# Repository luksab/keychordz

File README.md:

# Keychordz

This is my first completely custom keyboard hardware/software.

## Hardware

The hardware design is done in [KiCad](https://www.kicad.org/) and can be found in the hardware folder.

## Software

I started configuring [QMK](https://docs.qmk.fm/#/) for this hardware, but the chording features turned out to be too limiting, so I decided to write my own firmware from scratch in [Rust](https://rust-lang.org/).

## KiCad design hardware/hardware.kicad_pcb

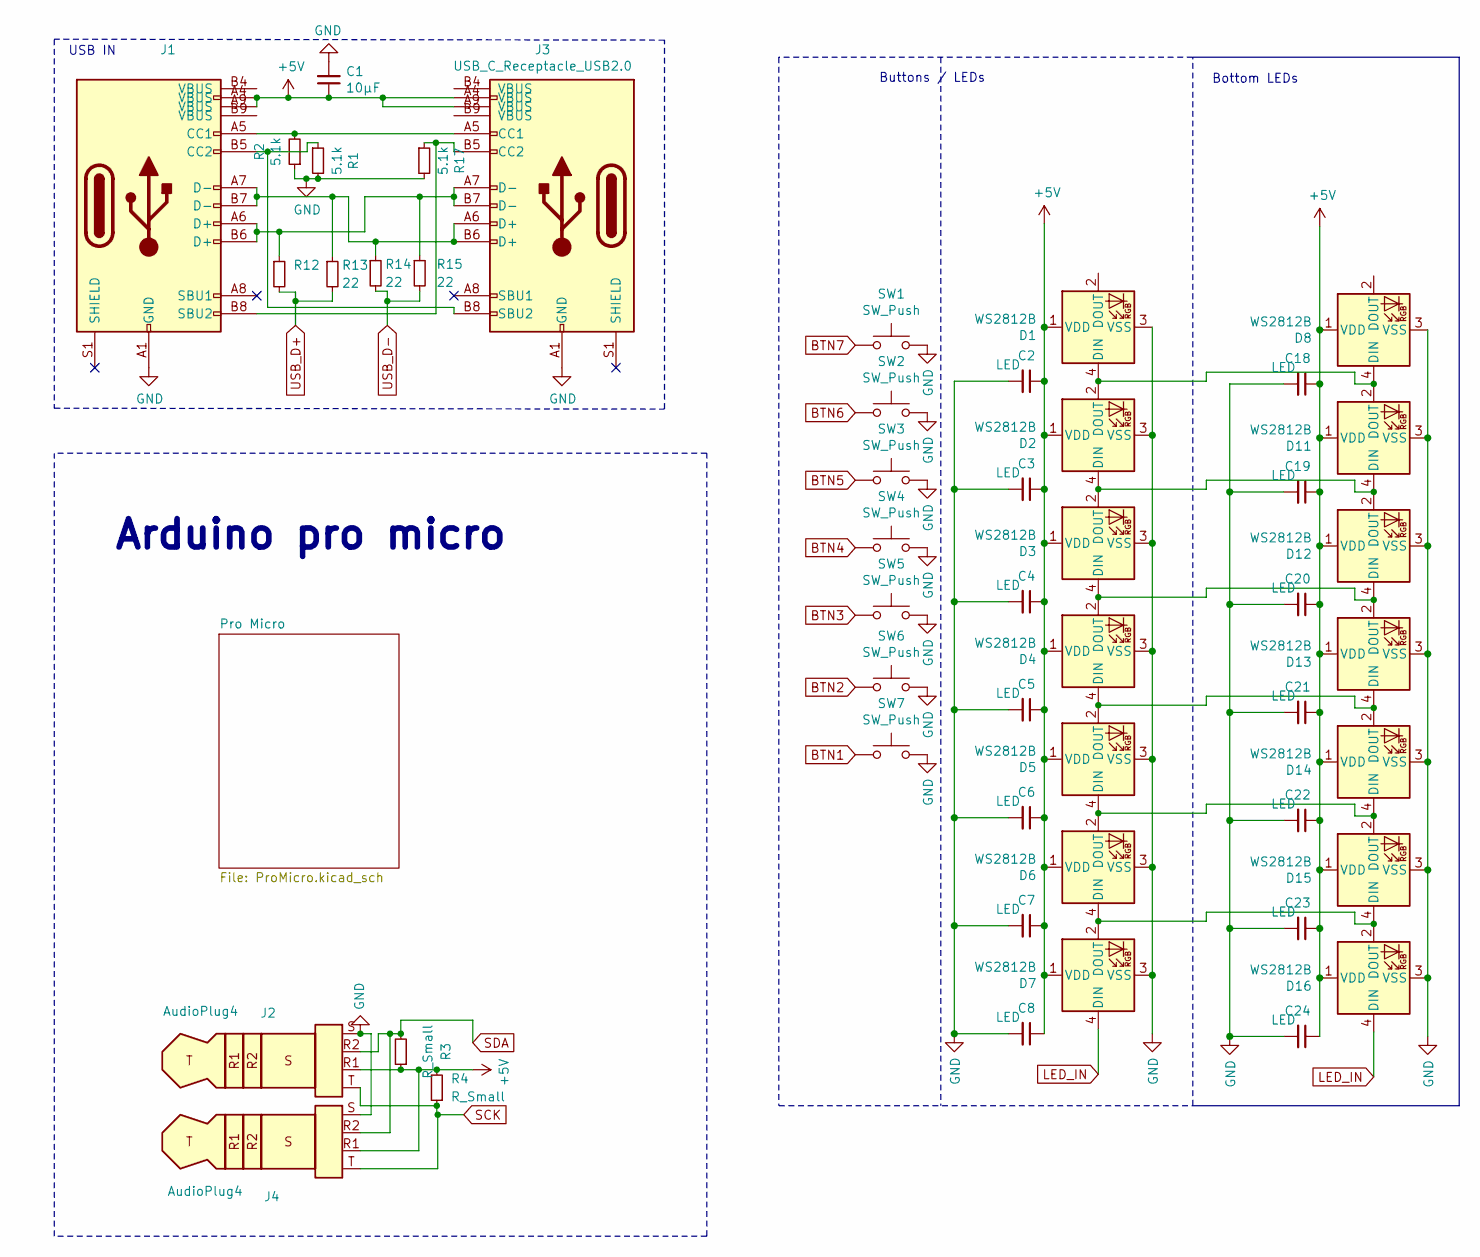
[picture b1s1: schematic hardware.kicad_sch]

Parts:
C1: 10µF; C_0805_2012Metric_Pad1.18x1.45mm_HandSolder
C2, C3, C4, C5, C6, C7, C8, C18, C19, C20, C21, C22, C23, C24: LED; C_0603_1608Metric_Pad1.08x0.95mm_HandSolder
D1, D2, D3, D4, D5, D6, D7, D8, D11, D12, D13, D14, D15, D16: WS2812B; LED_WS2812B_PLCC4_2.2x2.2mm
J1: (no value)
J2, J4: AudioPlug4; Jack_3.5mm_PJ320D_Horizontal
J3: USB_C_Receptacle_USB2.0; SS52400002
R1, R2, R17: 5.1k; R_0603_1608Metric_Pad0.98x0.95mm_HandSolder
R3, R4: R_Small; R_0603_1608Metric_Pad0.98x0.95mm_HandSolder
R12: (no value)
R13, R14, R15: 22; R_0603_1608Metric_Pad0.98x0.95mm_HandSolder
SW1, SW2, SW3, SW4, SW5, SW6, SW7: SW_Push; SW_PG1350

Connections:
+5V: C1.1, C2.1, C3.1, C4.1, C5.1, C6.1, C7.1, C8.1, C18.1, C19.1, C20.1, C21.1, C22.1, C23.1, C24.1, D1.1 (VDD), D2.1 (VDD), D3.1 (VDD), D4.1 (VDD), D5.1 (VDD), D6.1 (VDD), D7.1 (VDD), D8.1 (VDD), D11.1 (VDD), D12.1 (VDD), D13.1 (VDD), D14.1 (VDD), D15.1 (VDD), D16.1 (VDD), J1.A4 (VBUS), J1.A9 (VBUS), J2.R1, J3.A4 (VBUS), J3.A9 (VBUS), J4.R1, R3.1, R4.2; also elsewhere on the board
BTN1: SW7.1; also elsewhere on the board
BTN2: SW6.1; also elsewhere on the board
BTN3: SW5.1; also elsewhere on the board
BTN4: SW4.1; also elsewhere on the board
BTN5: SW3.1; also elsewhere on the board
BTN6: SW2.1; also elsewhere on the board
BTN7: SW1.1; also elsewhere on the board
GND: C1.2, C2.2, C3.2, C4.2, C5.2, C6.2, C7.2, C8.2, C18.2, C19.2, C20.2, C21.2, C22.2, C23.2, C24.2, D1.3 (VSS), D2.3 (VSS), D3.3 (VSS), D4.3 (VSS), D5.3 (VSS), D6.3 (VSS), D7.3 (VSS), D8.3 (VSS), D11.3 (VSS), D12.3 (VSS), D13.3 (VSS), D14.3 (VSS), D15.3 (VSS), D16.3 (VSS), J1.A1 (GND), J1.A12 (GND), J1.B1 (GND), J1.B12 (GND), J2.S, J3.A1 (GND), J3.A12 (GND), J3.B1 (GND), J3.B12 (GND), J4.S, R1.2, R2.1, R17.2, SW1.2, SW2.2, SW3.2, SW4.2, SW5.2, SW6.2, SW7.2; also elsewhere on the board
LED_IN: D7.4 (DIN), D16.4 (DIN); also elsewhere on the board
unnamed: D1.4 (DIN), D2.2 (DOUT), D8.4 (DIN), D11.2 (DOUT)
unnamed: D2.4 (DIN), D3.2 (DOUT), D11.4 (DIN), D12.2 (DOUT)
unnamed: D3.4 (DIN), D4.2 (DOUT), D12.4 (DIN), D13.2 (DOUT)
unnamed: D4.4 (DIN), D5.2 (DOUT), D13.4 (DIN), D14.2 (DOUT)
unnamed: D6.4 (DIN), D7.2 (DOUT), D15.4 (DIN), D16.2 (DOUT)
unnamed: D5.4 (DIN), D6.2 (DOUT), D14.4 (DIN), D15.2 (DOUT)
unnamed: J1.A5 (CC1), J3.A5 (CC1), R2.2
unnamed: J1.B5 (CC2), J3.B8 (SBU2), R1.1
unnamed: J1.B8 (SBU2), J3.B5 (CC2), R17.1
unnamed 40: J1.A7 (D-), J1.B7 (D-), J3.A6 (D+), J3.B6 (D+), R13.1, R14.1; also elsewhere on the board
unnamed 43: J1.A6 (D+), J1.B6 (D+), J3.A7 (D-), J3.B7 (D-), R12.1, R15.1; also elsewhere on the board
SCK: J2.T, J4.T, R4.1; also elsewhere on the board
SDA: J2.R2, J4.R2, R3.2; also elsewhere on the board
USB_D+: R12.2, R13.2; also elsewhere on the board
USB_D-: R14.2, R15.2; also elsewhere on the board

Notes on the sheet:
Arduino pro micro
Buttons / LEDs
Bottom LEDs
USB IN

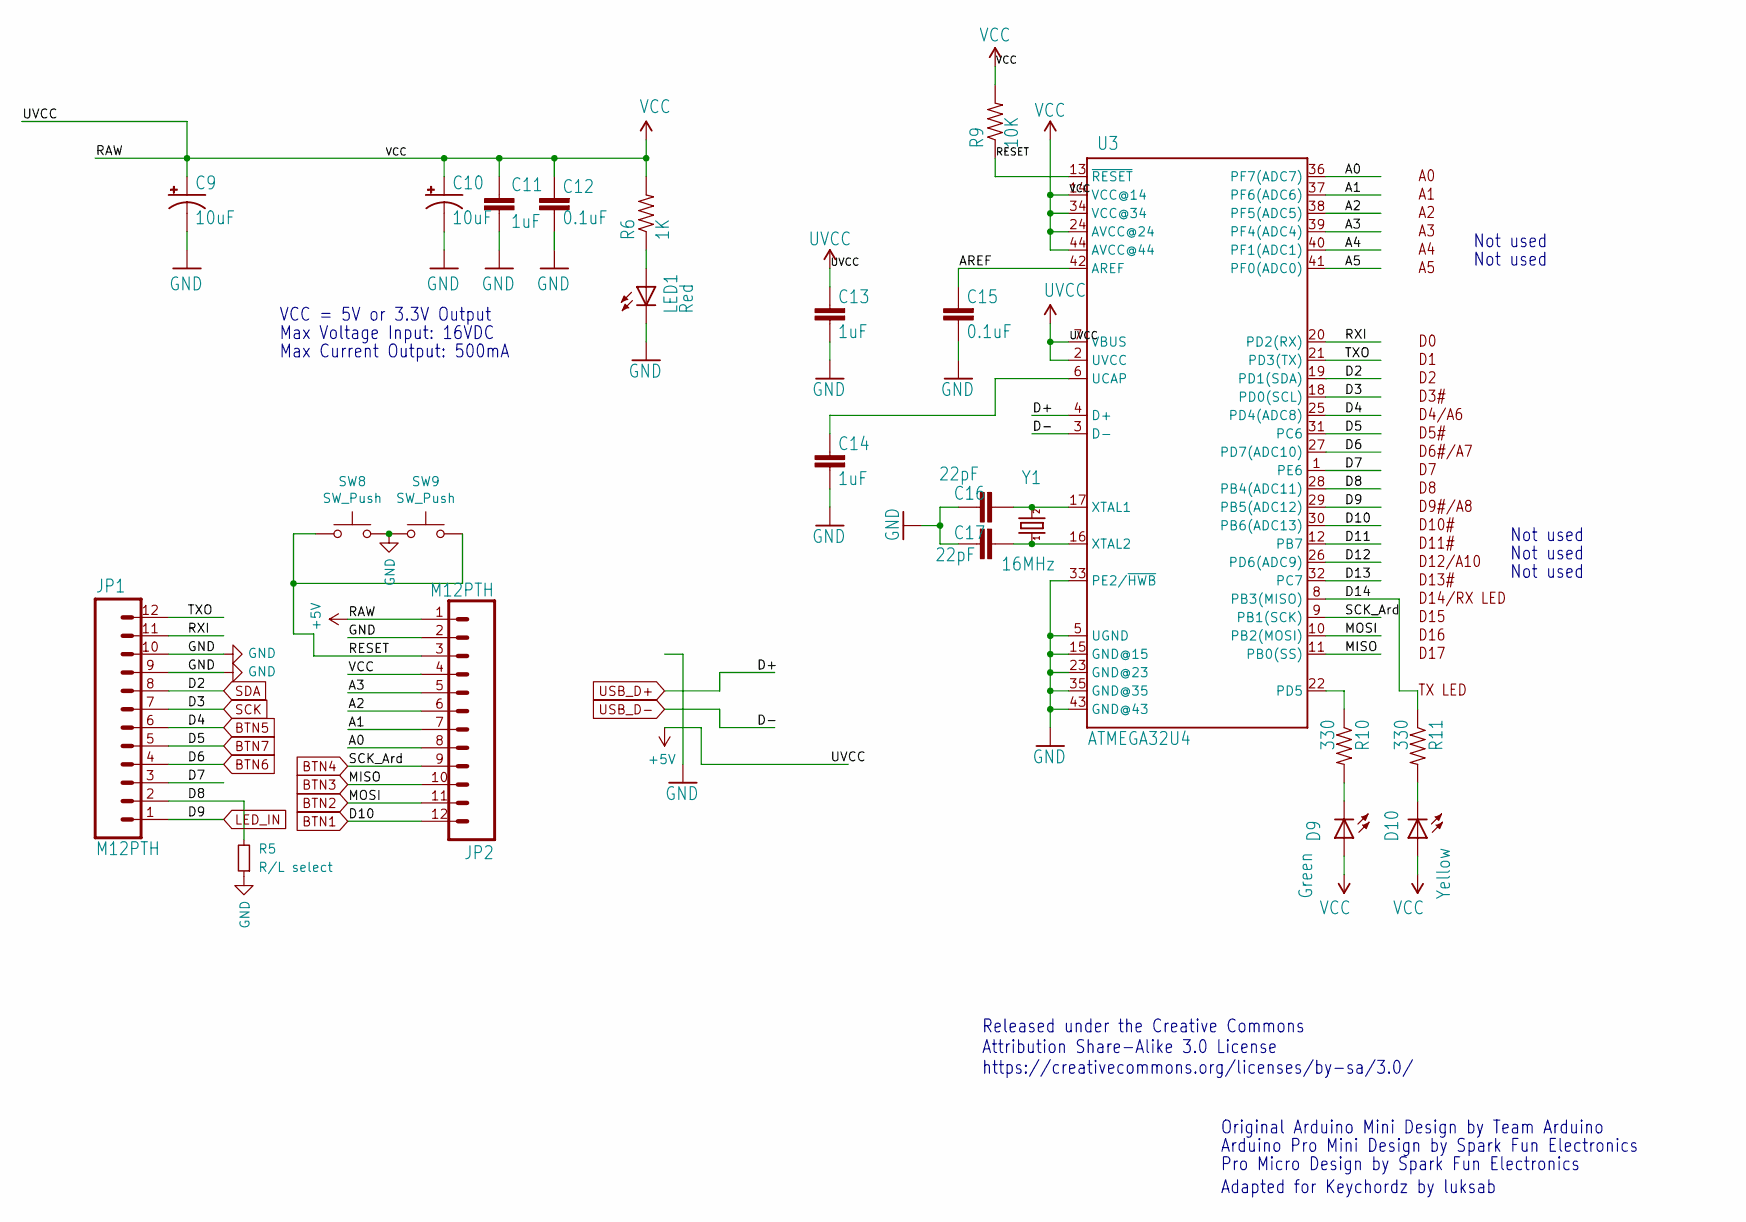
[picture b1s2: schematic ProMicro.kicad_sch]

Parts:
C9, C10: 10uF; EIA3216
C11, C13, C14: 1uF; C_0603_1608Metric_Pad1.08x0.95mm_HandSolder
C12, C15: 0.1uF; C_0603_1608Metric_Pad1.08x0.95mm_HandSolder
C16, C17: 22pF; C_0603_1608Metric_Pad1.08x0.95mm_HandSolder
D9: Green; LED_0603_1608Metric_Pad1.05x0.95mm_HandSolder
D10: Yellow; LED_0603_1608Metric_Pad1.05x0.95mm_HandSolder
JP1, JP2: M12PTH; PinHeader_1x12_P2.54mm_Vertical
LED1: Red; LED_0603_1608Metric_Pad1.05x0.95mm_HandSolder
R5: R/L select; R_0805_2012Metric_Pad1.20x1.40mm_HandSolder
R6: 1K; R_0603_1608Metric_Pad0.98x0.95mm_HandSolder
R9: 10K; R_0603_1608Metric_Pad0.98x0.95mm_HandSolder
R10, R11: 330; R_0603_1608Metric_Pad0.98x0.95mm_HandSolder
SW8, SW9: SW_Push; SW_SPST_CK_RS282G05A3
U3: ATMEGA32U4; QFN-44-NOPAD_1_1-OUTFAKES
Y1: 16MHz; CRYSTAL-SMD-5X3

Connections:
+5V: C9.A (+), C10.A (+), C11.1, C12.2, C13.2, D9.2 (A), D10.2 (A), JP2.1, JP2.4, R6.2, R9.2, U3.2 (UVCC), U3.7 (VBUS), U3.14 (VCC@14), U3.24 (AVCC@24), U3.34 (VCC@34), U3.44 (AVCC@44); also elsewhere on the board
/Pro Micro/A0: JP2.8, U3.36 (PF7(ADC7))
/Pro Micro/A1: JP2.7, U3.37 (PF6(ADC6))
/Pro Micro/A2: JP2.6, U3.38 (PF5(ADC5))
/Pro Micro/A3: JP2.5, U3.39 (PF4(ADC4))
/Pro Micro/A4: U3.40 (PF1(ADC1))
/Pro Micro/A5: U3.41 (PF0(ADC0))
/Pro Micro/AREF: C15.2, U3.42 (AREF)
/Pro Micro/D7: JP1.3, U3.1 (PE6)
/Pro Micro/D8: JP1.2, R5.2, U3.28 (PB4(ADC11))
/Pro Micro/D11: U3.12 (PB7)
/Pro Micro/D12: U3.26 (PD6(ADC9))
/Pro Micro/D13: U3.32 (PC7)
/Pro Micro/D14: R11.1, U3.8 (PB3(MISO))
/Pro Micro/RESET: JP2.3, R9.1, SW8.1, SW9.2, U3.13 (~RESET)
/Pro Micro/RXI: JP1.11, U3.20 (PD2(RX))
/Pro Micro/TXO: JP1.12, U3.21 (PD3(TX))
BTN1: JP2.12, U3.30 (PB6(ADC13)); also elsewhere on the board
BTN2: JP2.11, U3.10 (PB2(MOSI)); also elsewhere on the board
BTN3: JP2.10, U3.11 (PB0(SS)); also elsewhere on the board
BTN4: JP2.9, U3.9 (PB1(SCK)); also elsewhere on the board
BTN5: JP1.6, U3.25 (PD4(ADC8)); also elsewhere on the board
BTN6: JP1.4, U3.27 (PD7(ADC10)); also elsewhere on the board
BTN7: JP1.5, U3.31 (PC6); also elsewhere on the board
GND: C9.C (-), C10.C (-), C11.2, C12.1, C13.1, C14.1, C15.1, C16.2, C17.2, JP1.9, JP1.10, JP2.2, LED1.1 (C), R5.1, SW8.2, SW9.1, U3.5 (UGND), U3.15 (GND@15), U3.23 (GND@23), U3.33 (PE2/~HWB), U3.35 (GND@35), U3.43 (GND@43); also elsewhere on the board
LED_IN: JP1.1, U3.29 (PB5(ADC12)); also elsewhere on the board
unnamed: C14.2, U3.6 (UCAP)
unnamed: C16.1, U3.17 (XTAL1), Y1.3 (2)
unnamed: C17.1, U3.16 (XTAL2), Y1.1
unnamed: D9.1 (K), R10.2
unnamed: D10.1 (K), R11.2
unnamed: LED1.2 (A), R6.1
unnamed: R10.1, U3.22 (PD5)
SCK: JP1.7, U3.18 (PD0(SCL)); also elsewhere on the board
SDA: JP1.8, U3.19 (PD1(SDA)); also elsewhere on the board
USB_D+: U3.4 (D+); also elsewhere on the board
USB_D-: U3.3 (D-); also elsewhere on the board

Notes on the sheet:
VCC = 5V or 3.3V Output
Arduino Pro Mini Design by Spark Fun Electronics
Original Arduino Mini Design by Team Arduino
Released under the Creative Commons Attribution Share-Alike 3.0 License https://creativecommons.org/licenses/by-sa/3.0/
Pro Micro Design by Spark Fun Electronics
Adapted for Keychordz by luksab
Not used
Max Current Output: 500mA
Max Voltage Input: 16VDC

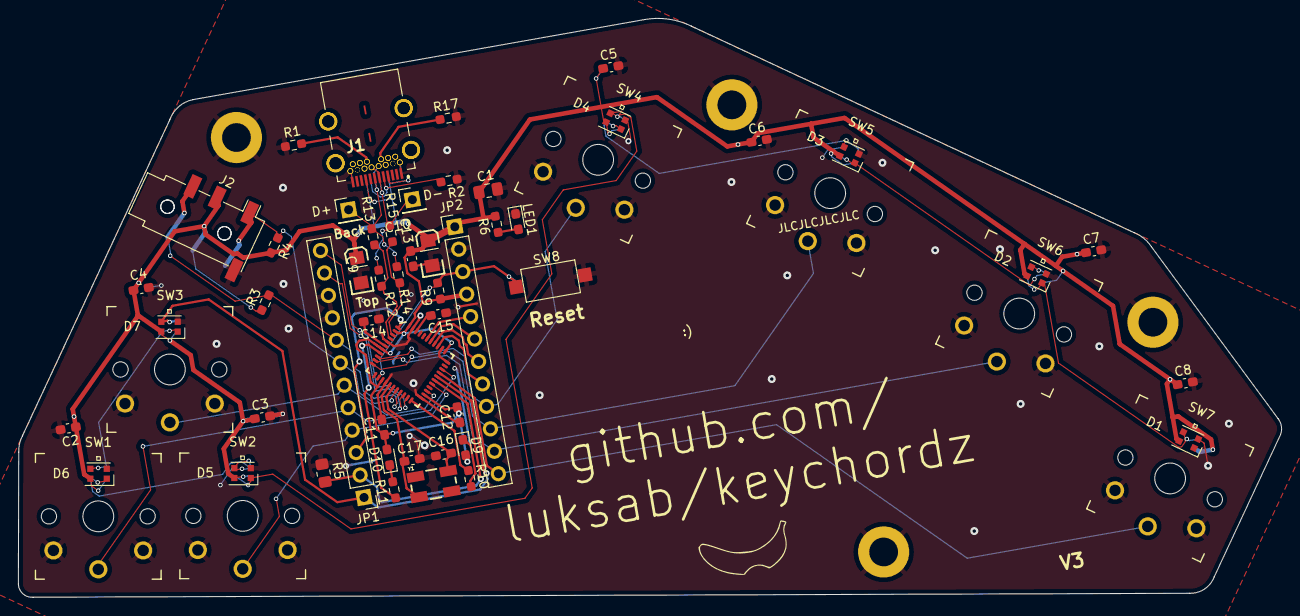
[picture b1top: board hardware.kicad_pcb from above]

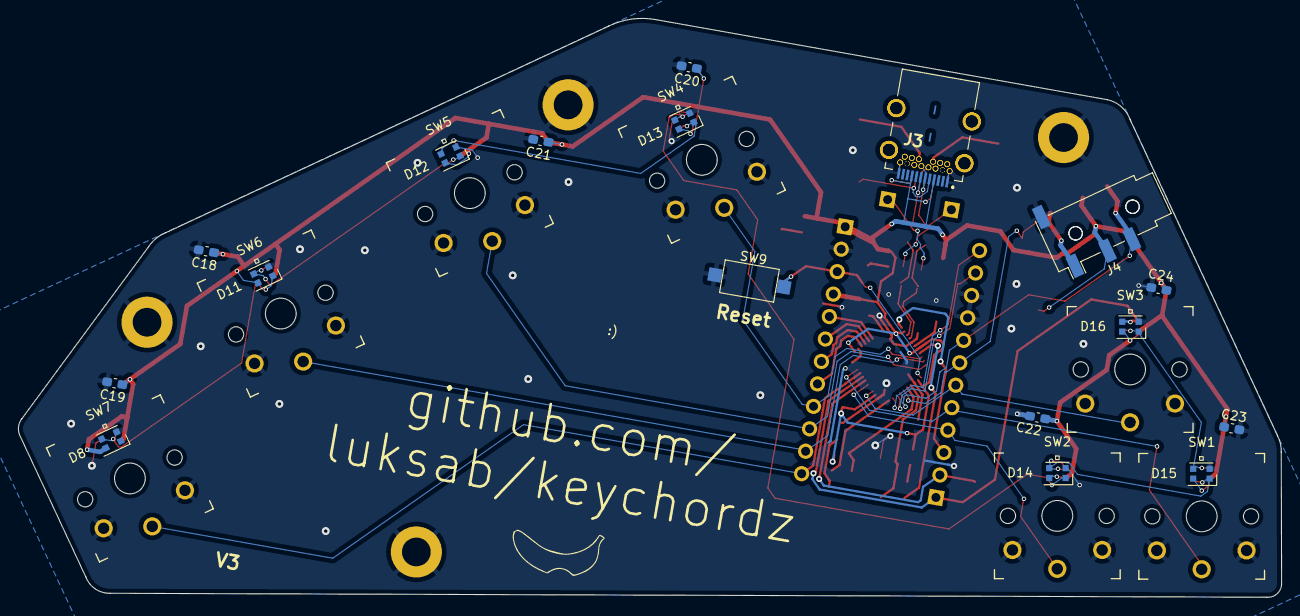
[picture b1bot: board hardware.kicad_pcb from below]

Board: 2 copper layers, 140.8 x 64.5 mm, 74 parts (17 on the bottom side), 43 nets.

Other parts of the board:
D+: PinHeader_1x01_P2.54mm_Vertical
D-: PinHeader_1x01_P2.54mm_Vertical

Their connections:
unnamed 40: D+.1; also elsewhere on the board
unnamed 43: D-.1; also elsewhere on the board

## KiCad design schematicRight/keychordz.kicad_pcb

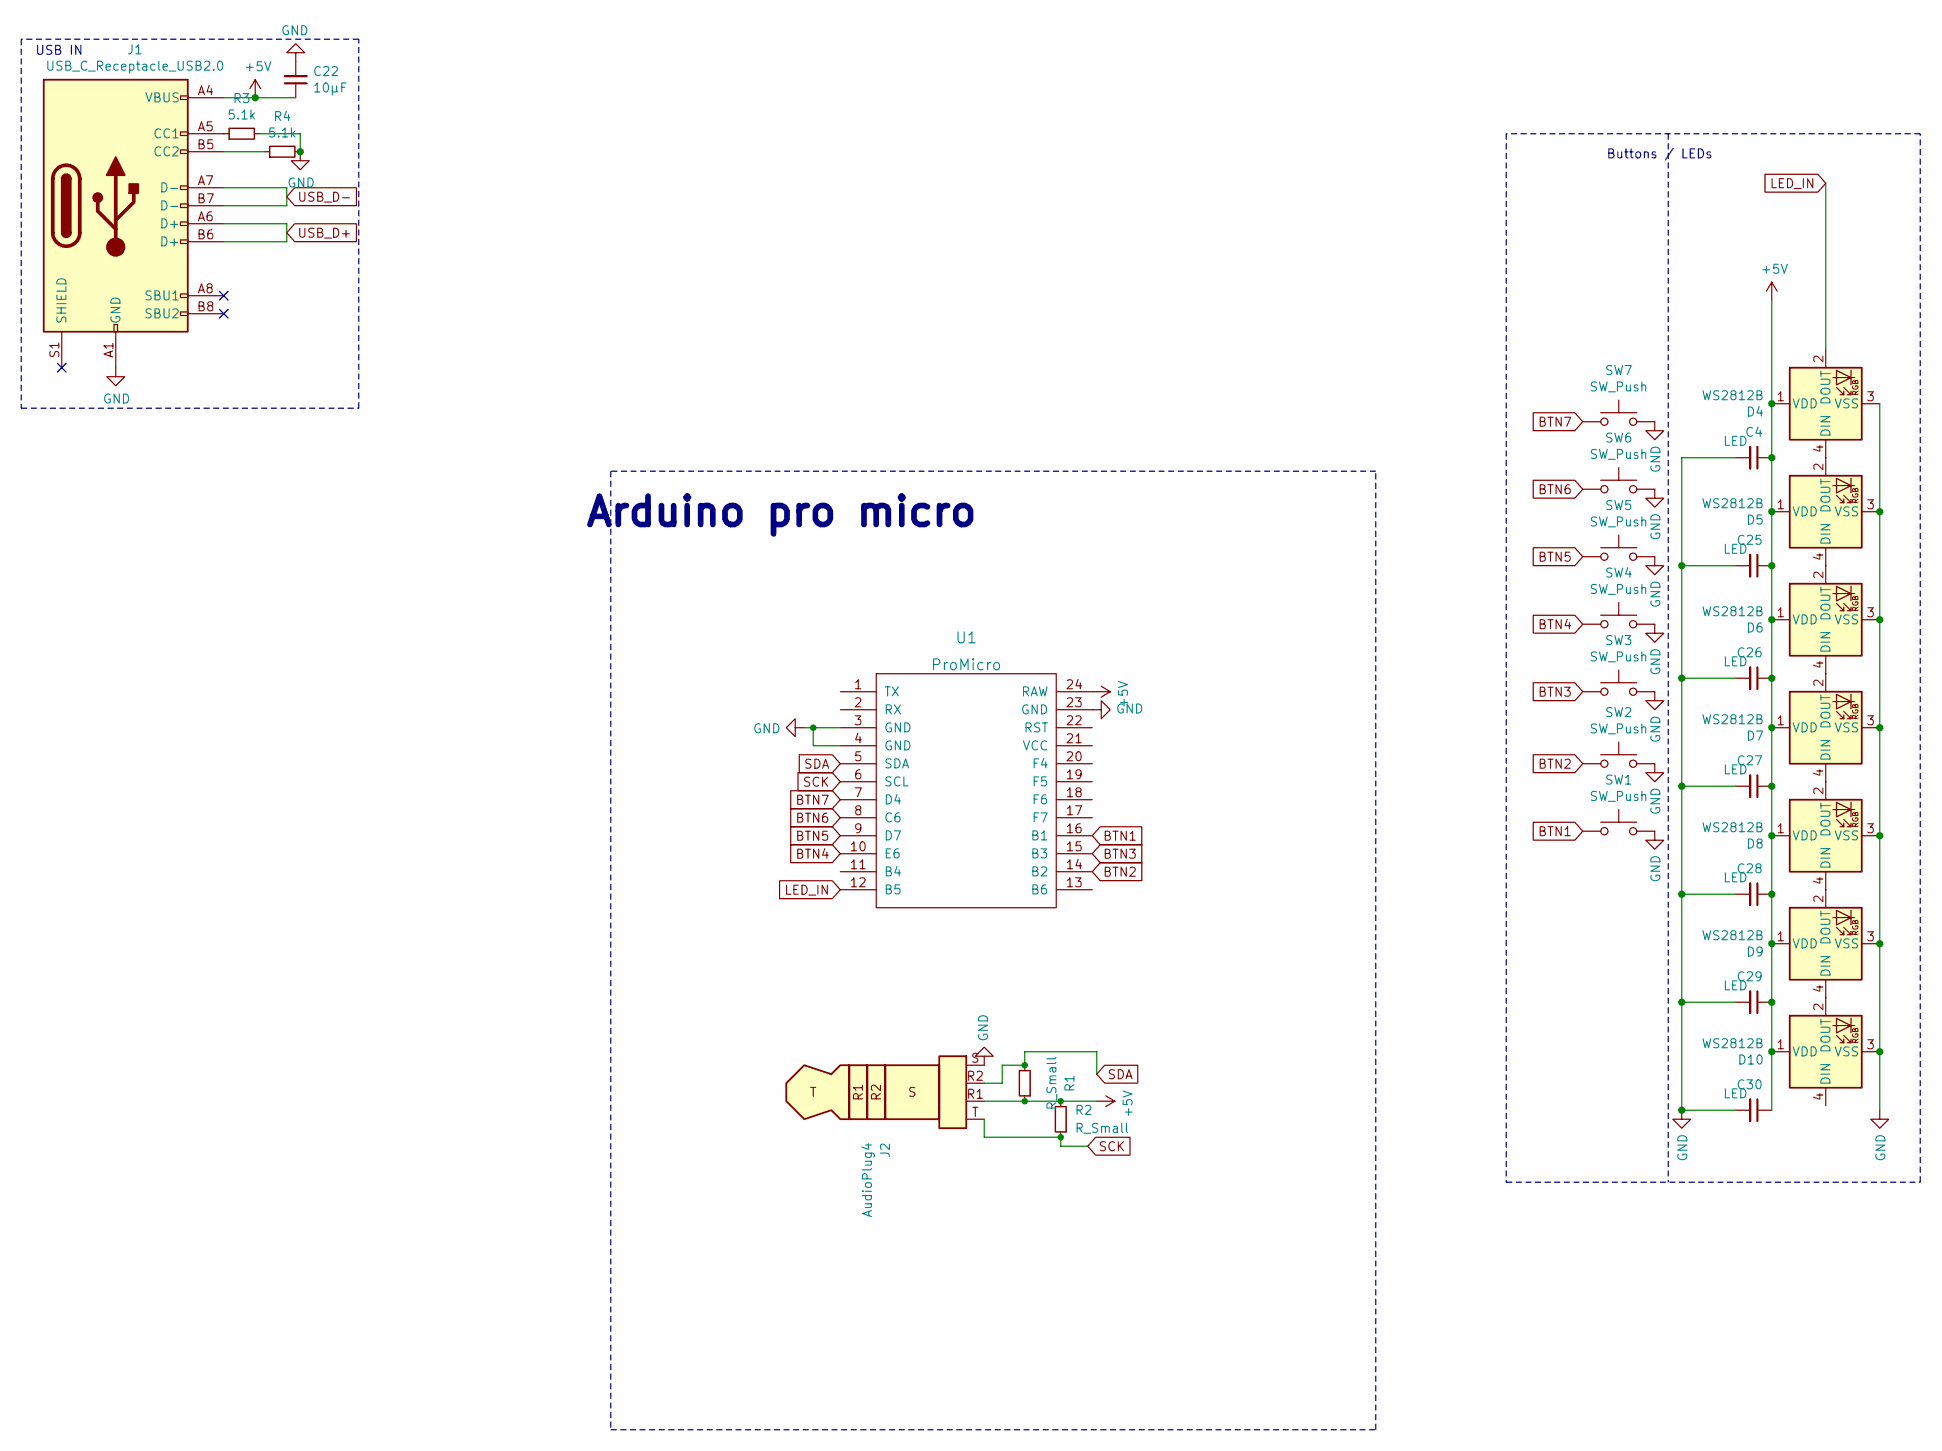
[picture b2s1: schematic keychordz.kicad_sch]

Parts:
C4, C25, C26, C27, C28, C29, C30: LED; C_0603_1608Metric_Pad1.08x0.95mm_HandSolder
C22: 10µF; C_0805_2012Metric_Pad1.18x1.45mm_HandSolder
D4, D5, D6, D7, D8, D9, D10: WS2812B; LED_WS2812B_PLCC4_2.2x2.2mm
J1: USB_C_Receptacle_USB2.0; SS52400002
J2: AudioPlug4; Jack_3.5mm_PJ320D_Horizontal
R1, R2: R_Small; R_0603_1608Metric_Pad0.98x0.95mm_HandSolder
R3, R4: 5.1k; R_0603_1608Metric_Pad0.98x0.95mm_HandSolder
SW1, SW2, SW3, SW4, SW5, SW6, SW7: SW_Push; SW_PG1350
U1: ProMicro

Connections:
+5V: C4.1, C22.1, C25.1, C26.1, C27.1, C28.1, C29.1, C30.1, D4.1 (VDD), D5.1 (VDD), D6.1 (VDD), D7.1 (VDD), D8.1 (VDD), D9.1 (VDD), D10.1 (VDD), J1.A4 (VBUS), J2.R1, R1.1, R2.2, U1.24 (RAW)
BTN1: SW1.1, U1.16 (B1)
BTN2: SW2.1, U1.14 (B2)
BTN3: SW3.1, U1.15 (B3)
BTN4: SW4.1, U1.10 (E6)
BTN5: SW5.1, U1.9 (D7)
BTN6: SW6.1, U1.8 (C6)
BTN7: SW7.1, U1.7 (D4)
GND: C4.2, C22.2, C25.2, C26.2, C27.2, C28.2, C29.2, C30.2, D4.3 (VSS), D5.3 (VSS), D6.3 (VSS), D7.3 (VSS), D8.3 (VSS), D9.3 (VSS), D10.3 (VSS), J1.A1 (GND), J2.S, R3.2, R4.2, SW1.2, SW2.2, SW3.2, SW4.2, SW5.2, SW6.2, SW7.2, U1.3 (GND), U1.4 (GND), U1.23 (GND)
LED_IN: D4.2 (DOUT), U1.12 (B5)
unnamed: D4.4 (DIN), D5.2 (DOUT)
unnamed: D5.4 (DIN), D6.2 (DOUT)
unnamed: D6.4 (DIN), D7.2 (DOUT)
unnamed: D7.4 (DIN), D8.2 (DOUT)
unnamed: D8.4 (DIN), D9.2 (DOUT)
unnamed: D9.4 (DIN), D10.2 (DOUT)
unnamed: J1.A5 (CC1), R3.1
unnamed: J1.B5 (CC2), R4.1
SCK: J2.T, R2.1, U1.6 (SCL)
SDA: J2.R2, R1.2, U1.5 (SDA)
USB_D+: J1.A6 (D+), J1.B6 (D+); also elsewhere on the board
USB_D-: J1.A7 (D-), J1.B7 (D-); also elsewhere on the board

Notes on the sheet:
USB IN
Buttons / LEDs
Arduino pro micro

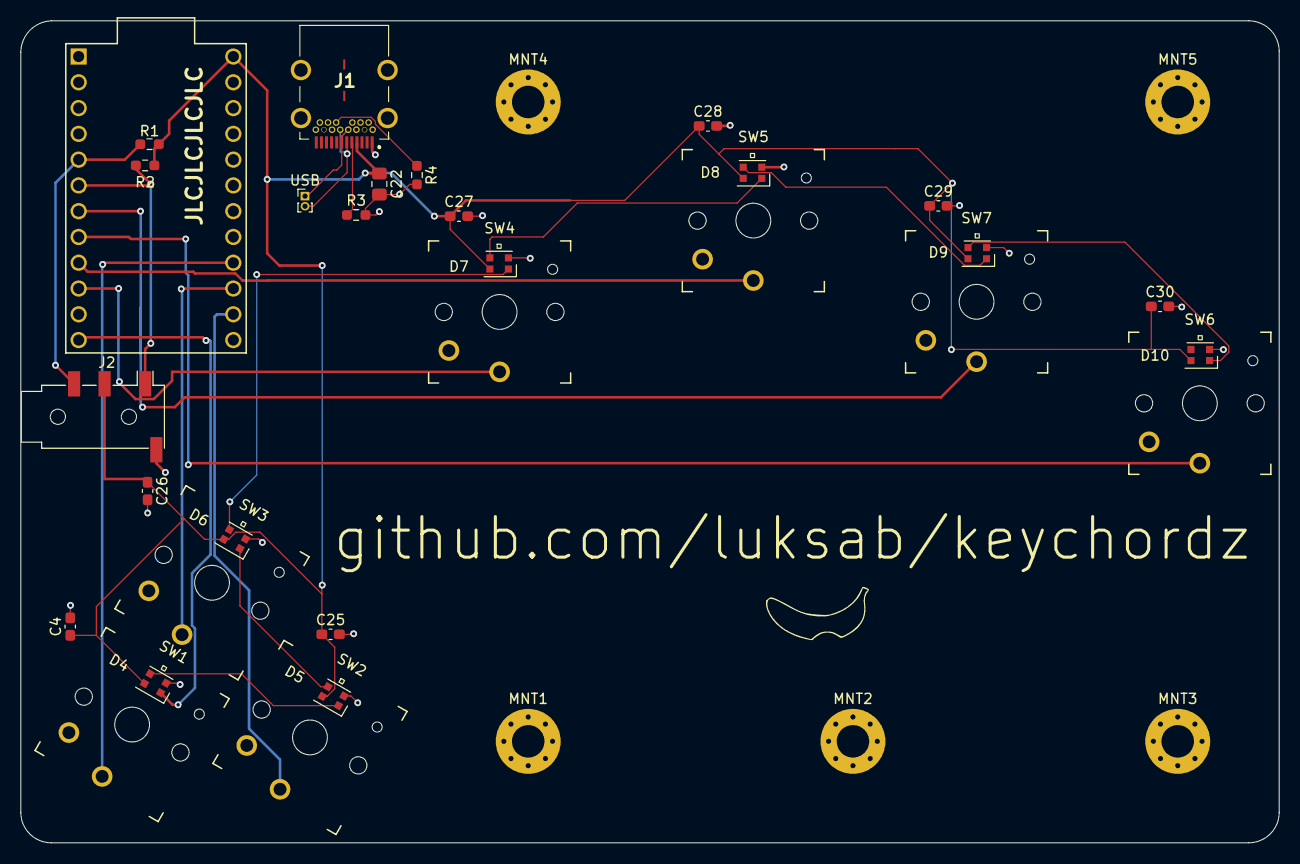
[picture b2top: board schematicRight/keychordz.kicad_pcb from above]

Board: 2 copper layers, 124.0 x 81.0 mm, 35 parts (0 on the bottom side), 22 nets.

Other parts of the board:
MNT1, MNT2, MNT3, MNT4, MNT5: MountingHole_3.2mm_M3_Pad_Via
USB: PinHeader_1x02_P1.00mm_Vertical

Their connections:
USB_D+: USB.2; also elsewhere on the board
USB_D-: USB.1; also elsewhere on the board

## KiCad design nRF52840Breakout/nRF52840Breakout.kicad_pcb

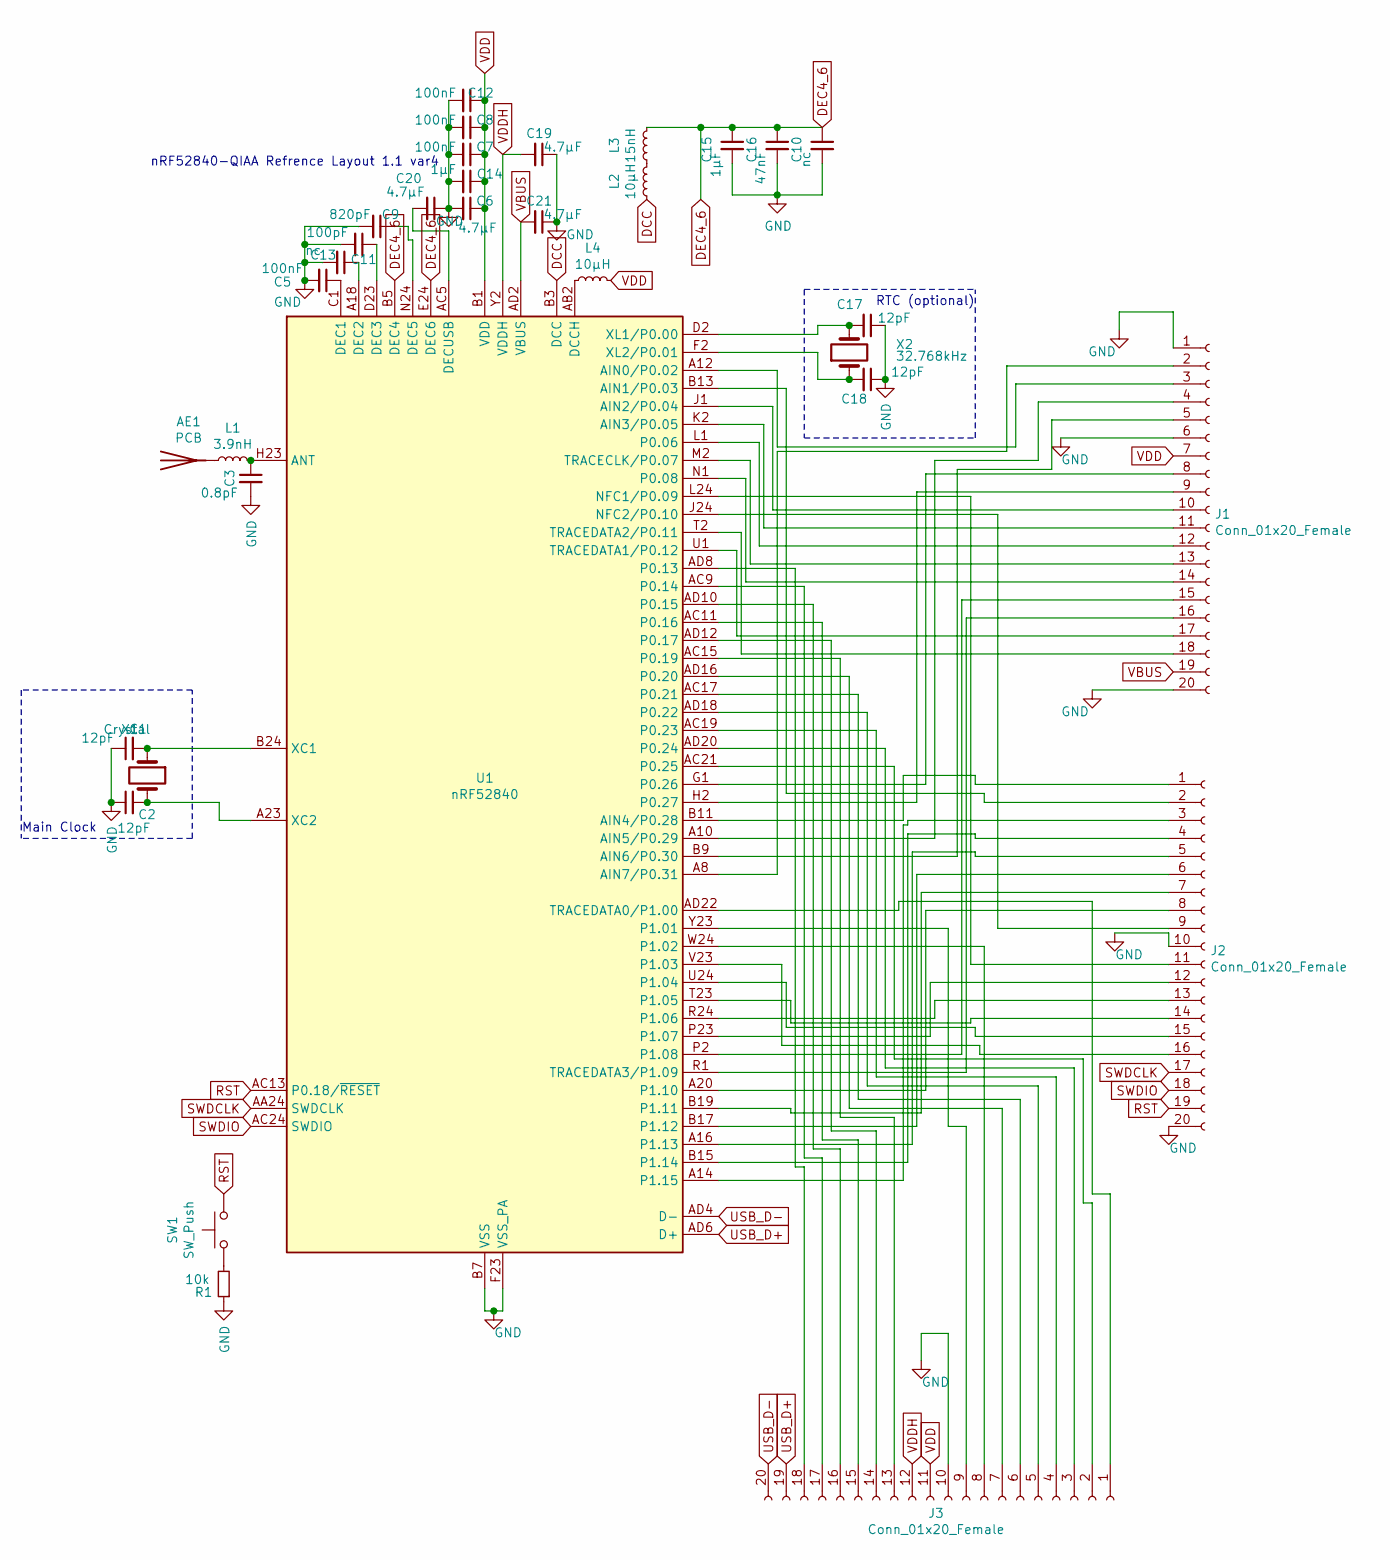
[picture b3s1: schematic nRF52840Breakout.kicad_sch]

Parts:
AE1: PCB; Texas_SWRA117D_2.4GHz_Left
C1, C2, C17, C18: 12pF; C_0402_1005Metric_Pad0.74x0.62mm_HandSolder
C3: 0.8pF; C_0201_0603Metric_Pad0.64x0.40mm_HandSolder
C5, C7, C8, C12: 100nF; C_0402_1005Metric_Pad0.74x0.62mm_HandSolder
C6, C20: 4.7µF; C_1206_3216Metric_Pad1.33x1.80mm_HandSolder
C9: 820pF; C_0402_1005Metric_Pad0.74x0.62mm_HandSolder
C10, C13: nc; C_0402_1005Metric_Pad0.74x0.62mm_HandSolder
C11: 100pF; C_0603_1608Metric_Pad1.08x0.95mm_HandSolder
C14, C15: 1µF; C_0603_1608Metric_Pad1.08x0.95mm_HandSolder
C16: 47nF; C_0402_1005Metric_Pad0.74x0.62mm_HandSolder
C19, C21: 4.7µF; C_0603_1608Metric_Pad1.08x0.95mm_HandSolder
J1, J2, J3: Conn_01x20_Female; CastelatedHoles 1mm
L1: 3.9nH; L_0402_1005Metric_Pad0.77x0.64mm_HandSolder
L2, L4: 10µH; L_1210_3225Metric_Pad1.42x2.65mm_HandSolder
L3: 15nH; L_0402_1005Metric_Pad0.77x0.64mm_HandSolder
R1: 10k; R_0402_1005Metric_Pad0.72x0.64mm_HandSolder
SW1: SW_Push; SW_SPST_PTS636
U1: nRF52840; Nordic_AQFN-73-1EP_7x7mm_P0.5mm; LCSC C190794
X1: Crystal; XRCGB32M000F2P01R0
X2: 32.768kHz; Crystal_SMD_MicroCrystal_CC7V-T1A-2Pin_3.2x1.5mm_HandSolder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

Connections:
DCC: L2.1, U1.B3 (DCC)
DEC4_6: C10.1, C15.1, C16.1, L3.2, U1.B5 (DEC4), U1.E24 (DEC6)
GND: C1.1, C2.1, C3.2, C5.2, C6.2, C7.2, C8.2, C9.2, C10.2, C11.2, C12.2, C13.2, C14.2, C15.2, C16.2, C17.1, C18.1, C19.1, C20.1, C21.1, J1.1, J1.6, J1.20, J2.10, J2.20, J3.10, R1.1, U1.B7 (VSS), U1.EP (VSS), U1.F23 (VSS_PA)
unnamed: AE1.1 (A), L1.1
unnamed: C1.2, U1.B24 (XC1), X1.1
unnamed: C2.2, U1.A23 (XC2), X1.3
unnamed: C3.1, L1.2, U1.H23 (ANT)
unnamed: C5.1, U1.C1 (DEC1)
unnamed: C9.1, U1.N24 (DEC5)
unnamed: C11.1, U1.D23 (DEC3)
unnamed: C13.1, U1.A18 (DEC2)
unnamed: C17.2, U1.D2 (XL1/P0.00), X2.2
unnamed: C18.2, U1.F2 (XL2/P0.01), X2.1
unnamed: C20.2, U1.AC5 (DECUSB)
unnamed: J1.2, U1.A8 (AIN7/P0.31)
unnamed: J1.3, U1.A12 (AIN0/P0.02)
unnamed: J1.4, U1.A10 (AIN5/P0.29)
unnamed: J1.5, U1.B9 (AIN6/P0.30)
unnamed: J1.8, U1.G1 (P0.26)
unnamed: J1.9, U1.H2 (P0.27)
unnamed: J1.10, U1.J1 (AIN2/P0.04)
unnamed: J1.11, U1.K2 (AIN3/P0.05)
unnamed: J1.12, U1.L1 (P0.06)
unnamed: J1.13, U1.M2 (TRACECLK/P0.07)
unnamed: J1.14, U1.N1 (P0.08)
unnamed: J1.15, U1.P2 (P1.08)
unnamed: J1.16, U1.R1 (TRACEDATA3/P1.09)
unnamed: J1.17, U1.U1 (TRACEDATA1/P0.12)
unnamed: J1.18, U1.T2 (TRACEDATA2/P0.11)
unnamed: J2.1, U1.B11 (AIN4/P0.28)
unnamed: J2.2, U1.B13 (AIN1/P0.03)
unnamed: J2.3, U1.A14 (P1.15)
unnamed: J2.4, U1.B15 (P1.14)
unnamed: J2.5, U1.A16 (P1.13)
unnamed: J2.6, U1.B17 (P1.12)
unnamed: J2.7, U1.B19 (P1.11)
unnamed: J2.8, U1.A20 (P1.10)
unnamed: J2.9, U1.J24 (NFC2/P0.10)
unnamed: J2.11, U1.L24 (NFC1/P0.09)
unnamed: J2.12, U1.P23 (P1.07)
unnamed: J2.13, U1.R24 (P1.06)
unnamed: J2.14, U1.T23 (P1.05)
unnamed: J2.15, U1.U24 (P1.04)
unnamed: J2.16, U1.V23 (P1.03)
unnamed: J3.1, U1.AD22 (TRACEDATA0/P1.00)
unnamed: J3.2, U1.AC21 (P0.25)
unnamed: J3.3, U1.AD20 (P0.24)
unnamed: J3.4, U1.AC19 (P0.23)
unnamed: J3.5, U1.AD18 (P0.22)
unnamed: J3.6, U1.AC17 (P0.21)
unnamed: J3.7, U1.AD16 (P0.20)
unnamed: J3.8, U1.W24 (P1.02)
unnamed: J3.9, U1.Y23 (P1.01)
unnamed: J3.13, U1.AC15 (P0.19)
unnamed: J3.14, U1.AD12 (P0.17)
unnamed: J3.15, U1.AC11 (P0.16)
unnamed: J3.16, U1.AD10 (P0.15)
unnamed: J3.17, U1.AC9 (P0.14)
unnamed: J3.18, U1.AD8 (P0.13)
unnamed: L2.2, L3.1
unnamed: L4.1, U1.AB2 (DCCH)
unnamed: R1.2, SW1.1
RST: J2.19, SW1.2, U1.AC13 (P0.18/~RESET)
SWDCLK: J2.17, U1.AA24 (SWDCLK)
SWDIO: J2.18, U1.AC24 (SWDIO)
USB_D+: J3.19, U1.AD6 (D+)
USB_D-: J3.20, U1.AD4 (D-)
VBUS: C21.2, J1.19, U1.AD2 (VBUS)
VDD: C6.1, C7.1, C8.1, C12.1, C14.1, J1.7, J3.11, L4.2, U1.A22 (VDD), U1.AD14 (VDD), U1.AD23 (VDD), U1.B1 (VDD), U1.W1 (VDD)
VDDH: C19.2, J3.12, U1.Y2 (VDDH)

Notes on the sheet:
Main Clock
nRF52840-QIAA Refrence Layout 1.1 var4
RTC (optional)

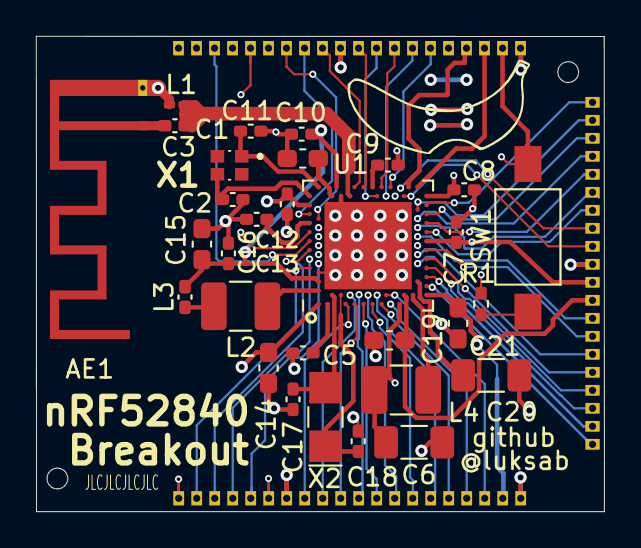
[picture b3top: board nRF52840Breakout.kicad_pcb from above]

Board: 4 copper layers, 31.6 x 26.4 mm, 33 parts (0 on the bottom side), 70 nets.
